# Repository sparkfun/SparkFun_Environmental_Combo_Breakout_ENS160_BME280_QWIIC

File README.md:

SparkFun Environmental Combo Breakout - ENS160/BME280 (Qwiic)
========================================

[*SparkFun Environmental Combo Breakout - ENS160/BME280 (Qwiic) (SEN-22858)*](https://www.sparkfun.com/products/22858)

Environmental sensor that includes the ENS160 and BME280.

Repository Contents
-------------------

* **/Documentation** - Data sheets, additional product information
* **/Hardware** - Eagle design files (.brd, .sch)
  * **/Production** - Production panel files (.brd)

Documentation
--------------
* **[ENS160 Library](https://github.com/sparkfun/SparkFun_Indoor_Air_Quality_Sensor-ENS160_Arduino_Library)** - Arduino library for the ENS160
* **[BME280 Library](https://github.com/sparkfun/SparkFun_BME280_Arduino_Library)** - Arduino library for the BME280
* **[Fritzing Part](https://github.com/sparkfun/Fritzing_Parts/blob/main/products/22858_sfe_qwiic_environmental_combo_ens160_bme280.fzpz)** - Fritzing Part for the Environmental Combo Breakout - ENS160/BME280.
* **[Hookup Guide](http://docs.sparkfun.com/SparkFun_Environmental_Combo_Breakout_ENS160_BME280_QWIIC/)** - Basic hookup guide for the Environmental Combo Breakout - ENS160/BME280.

Product Versions
----------------
* [SEN-22858](https://www.sparkfun.com/products/22858) - v1.1

Version History
---------------
* v1.0 - Initial Release

License Information
-------------------

This product is _**open source**_!

Please review the LICENSE.md file for license information.

If you have any questions or concerns on licensing, please contact technical support on our [SparkFun forums](https://forum.sparkfun.com/viewforum.php?f=152).

Distributed as-is; no warranty is given.

- Your friends at SparkFun.

_<COLLABORATION CREDIT>_

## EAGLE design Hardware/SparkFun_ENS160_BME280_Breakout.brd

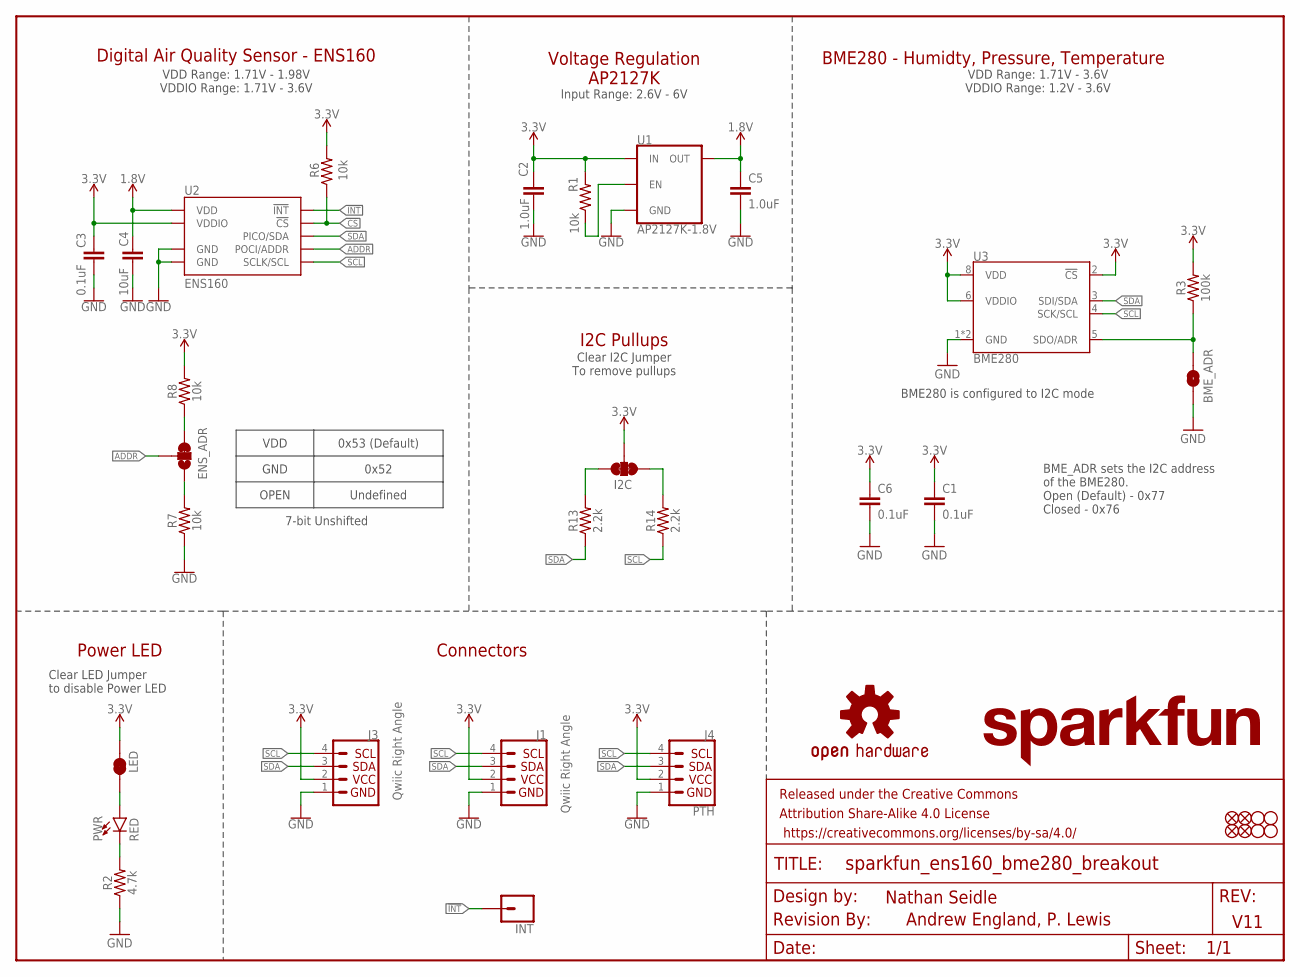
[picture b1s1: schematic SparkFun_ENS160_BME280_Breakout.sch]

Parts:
BME_ADR: JUMPER-SMT_2_NO_SILK; SMT-JUMPER_2_NO_SILK
C1, C3, C6: 0.1uF; 0402-TIGHT
C2, C5: 1.0uF; 0402-TIGHT
C4: 10uF; 0402-TIGHT
ENS_ADR: JUMPER-SMT_3_1-NC_TRACE_SILK; SMT-JUMPER_3_1-NC_TRACE_SILK
FD1, FD2, FD3, FD4: FIDUCIAL1X2; FIDUCIAL-1X2
FRAME1: FRAME-LETTER; CREATIVE_COMMONS
H1, H2, H3, H4: STAND-OFF
I2C: JUMPER-SMT_3_2-NC_TRACE_SILK; SMT-JUMPER_3_2-NC_TRACE_SILK
INT: CONN_01PTH_NO_SILK_STAND; 1X01_NO_SILK_STAND
J1, J3: Qwiic Right Angle; JST04_1MM_RA
J4: PTH; 1X04_NO_SILK
LED: JUMPER-SMT_2_NC_TRACE_SILK; SMT-JUMPER_2_NC_TRACE_SILK
LOGO1: SFE_LOGO_NAME.1_INCH; SFE_LOGO_NAME_.1
LOGO2: REVISION
LOGO4: OSHW-LOGOS; OSHW-LOGO-S
PWR: RED; LED-0603
R1, R6, R7, R8: 10k; 0402-TIGHT
R2: 4.7k; 0402-TIGHT
R3: 100k; 0402-TIGHT
R13, R14: 2.2k; 0402-TIGHT
U1: AP2127K-1.8V; SOT23-5
U2: ENS160; LGA-9
U3: BME280; LGA-8-2.5X2.5

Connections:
1.8V: C4.1, C5.1, U1.5 (OUT), U2.P4 (VDD)
3.3V: C1.1, C2.1, C3.1, C6.1, I2C.2, J1.2, J3.2, J4.2, LED.1, R1.2, R3.2, R6.2, R8.2, U1.1 (IN), U2.P5 (VDDIO), U3.2 (!CS), U3.6 (VDDIO), U3.8 (VDD)
!CS!: R6.1, U2.P7 (!CS!)
!INT!: INT.1, U2.P6 (!INT!)
ADDR: ENS_ADR.2, U2.P3 (POCI/ADDR)
GND: BME_ADR.1, C1.2, C2.2, C3.2, C4.2, C5.2, C6.2, J1.1, J3.1, J4.1, R2.1, R7.1, U1.2 (GND), U2.P8 (GND), U2.P9 (GND), U3.1 (GND), U3.7 (GND)
unnamed: ENS_ADR.3, R8.1
unnamed: R1.1, U1.3 (EN)
unnamed: I2C.3, R13.2
unnamed: I2C.1, R14.2
unnamed: PWR.C, R2.2
unnamed: ENS_ADR.1, R7.2
unnamed: LED.2, PWR.A
SCL: J1.4, J3.4, J4.4, R14.1, U2.P2 (SCLK/SCL), U3.4 (SCK/SCL)
SDA: J1.3, J3.3, J4.3, R13.1, U2.P1 (PICO/SDA), U3.3 (SDI/SDA)
SDO/ADR: BME_ADR.2, R3.1, U3.5 (SDO/ADR)

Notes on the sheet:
Clear I2C Jumper To remove pullups
V11
Nathan Seidle
BME_ADR sets the I2C address of the BME280. Open (Default) - 0x77 Closed - 0x76
BME280 is configured to I2C mode
BME280 - Humidty, Pressure, Temperature
Andrew England, P. Lewis
Digital Air Quality Sensor - ENS160
VDD Range: 1.71V - 1.98V VDDIO Range: 1.71V - 3.6V
VDD
GND
OPEN
0x52
0x53 (Default)
Undefined
7-bit Unshifted
Voltage Regulation AP2127K
Input Range: 2.6V - 6V
Clear LED Jumper to disable Power LED
Power LED
I2C Pullups
Connectors
VDD Range: 1.71V - 3.6V VDDIO Range: 1.2V - 3.6V

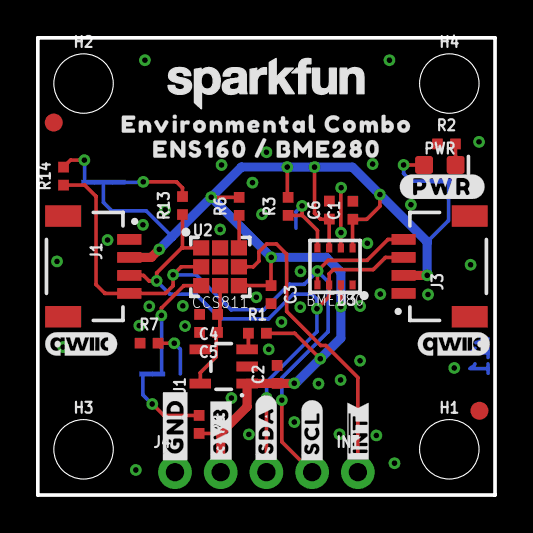
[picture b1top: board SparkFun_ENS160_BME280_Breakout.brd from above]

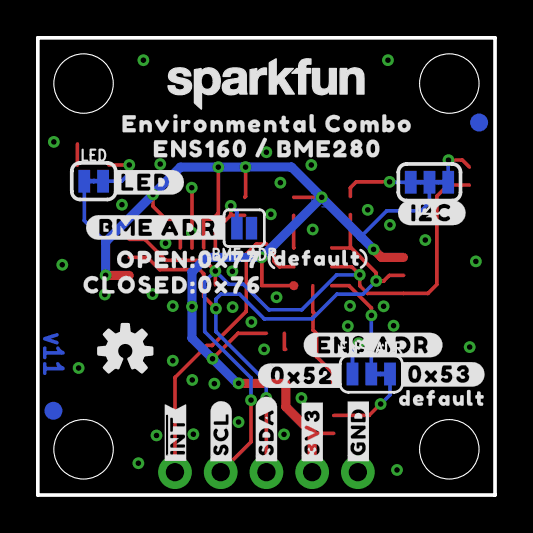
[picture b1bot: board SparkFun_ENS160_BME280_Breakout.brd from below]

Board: 2 copper layers, 25.4 x 25.4 mm, 67 parts (25 on the bottom side), 16 nets.

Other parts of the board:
LOGO3: SFE_LOGO_NAME.1_INCH; SFE_LOGO_NAME_.1@1
U$1: #BME_ADR#0
U$2: #0X53#0
U$3: #0X52#0
U$4: ##INT##6
U$5: #ENS_ADR#0
U$6: #I2C#0
U$7, U$11: ENVIRONMENTAL_COMBO0
U$8: #SCL#4
U$9: #GND#2
U$10, U$12: ENS160_#_BME2800
U$13, U$61: DEFAULT0
U$14: #SDA#3
U$15: #PWR#0
U$16: OPEN#0X770
U$17: CLOSED#0X760
U$18: #LED#0
U$20, U$21: QWIIC_4MM
U$27, U$46: #3V3#874
U$45: #GND#864
U$47: #SDA#874
U$48: #SCL#875
U$51: ##INT##877
U$59: ORDERING_INSTRUCTIONS

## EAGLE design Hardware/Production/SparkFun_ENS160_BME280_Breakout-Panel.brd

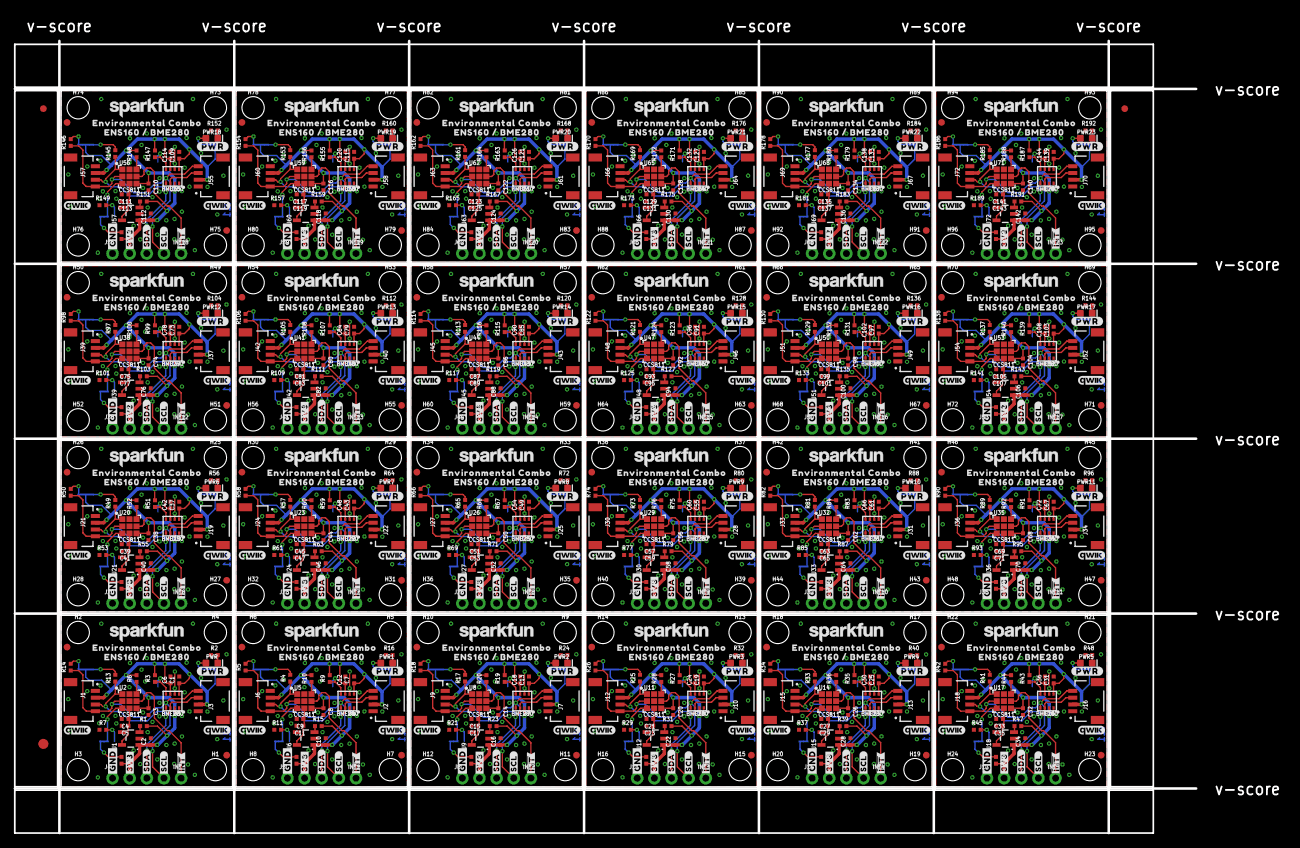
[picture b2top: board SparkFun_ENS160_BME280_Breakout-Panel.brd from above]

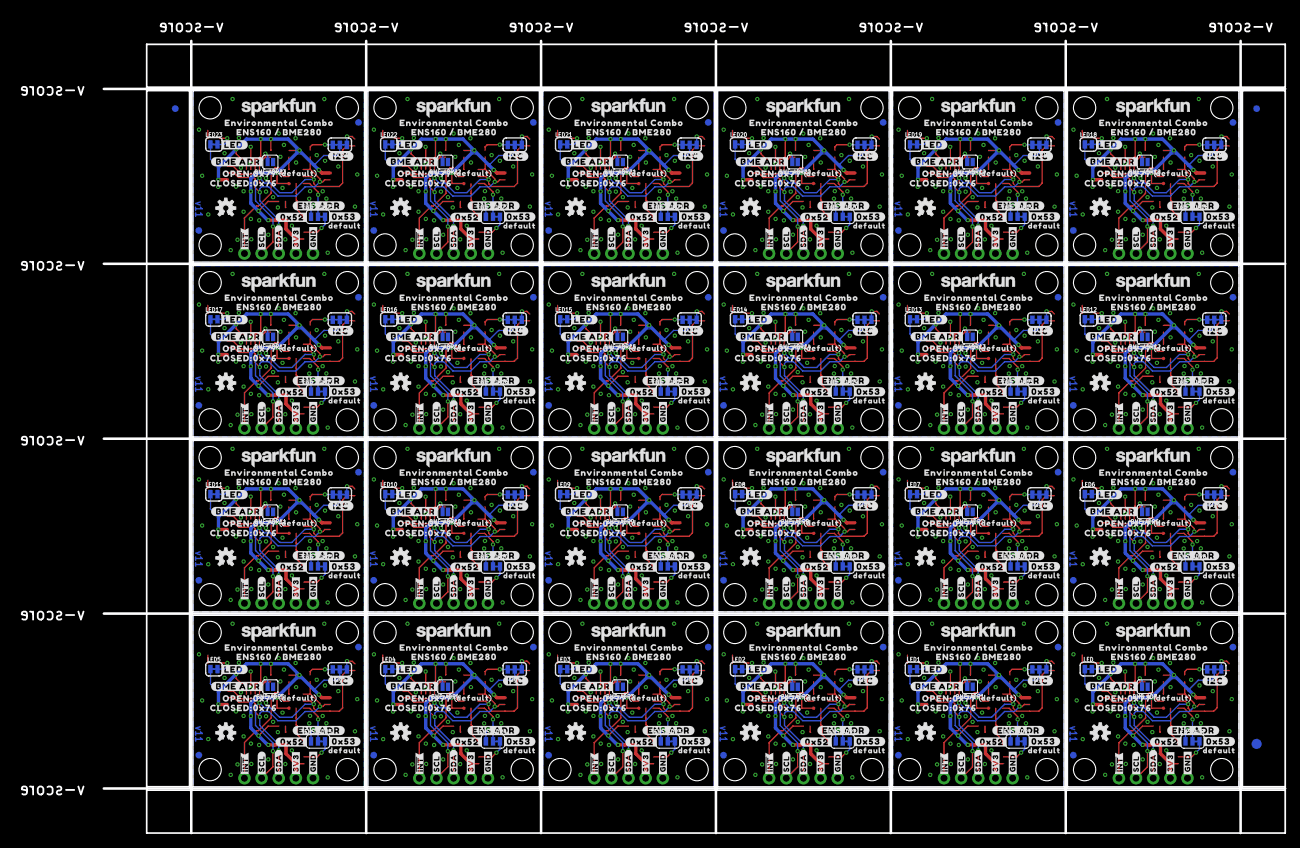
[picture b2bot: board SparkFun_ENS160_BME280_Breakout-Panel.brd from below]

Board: 2 copper layers, 188.2 x 121.2 mm, 1566 parts (603 on the bottom side), 384 nets.

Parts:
BME_ADR, BME_ADR1, BME_ADR2, BME_ADR3, BME_ADR4, BME_ADR5, BME_ADR6, BME_ADR7, BME_ADR8, BME_ADR9, BME_ADR10, BME_ADR11, BME_ADR12, BME_ADR13, BME_ADR14, BME_ADR15, BME_ADR16, BME_ADR17, BME_ADR18, BME_ADR19, BME_ADR20, BME_ADR21, BME_ADR22, BME_ADR23: SMT-JUMPER_2_NO_SILK
C1, C3, C6, C7, C8, C12, C13, C14, C18, C19, C20, C24, C25, C26, C30, C31, C32, C36, C37, C38, C42, C43, C44, C48, C49, C50, C54, C55, C56, C60, C61, C62, C66, C67, C68, C72, C73, C74, C78, C79, C80, C84, C85, C86, C90, C91, C92, C96, C97, C98, C102, C103, C104, C108, C109, C110, C114, C115, C116, C120, C121, C122, C126, C127, C128, C132, C133, C134, C138, C139, C140, C144: 0.1uF; 0402-TIGHT
C2, C5, C10, C11, C16, C17, C22, C23, C28, C29, C34, C35, C40, C41, C46, C47, C52, C53, C58, C59, C64, C65, C70, C71, C76, C77, C82, C83, C88, C89, C94, C95, C100, C101, C106, C107, C112, C113, C118, C119, C124, C125, C130, C131, C136, C137, C142, C143: 1.0uF; 0402-TIGHT
C4, C9, C15, C21, C27, C33, C39, C45, C51, C57, C63, C69, C75, C81, C87, C93, C99, C105, C111, C117, C123, C129, C135, C141: 10uF; 0402-TIGHT
E$1, E$2, E$3, E$4: FIDUCIAL-1X2
E$5, E$6: FIDUCIAL-1.5X3
ENS_ADR, ENS_ADR1, ENS_ADR2, ENS_ADR3, ENS_ADR4, ENS_ADR5, ENS_ADR6, ENS_ADR7, ENS_ADR8, ENS_ADR9, ENS_ADR10, ENS_ADR11, ENS_ADR12, ENS_ADR13, ENS_ADR14, ENS_ADR15, ENS_ADR16, ENS_ADR17, ENS_ADR18, ENS_ADR19, ENS_ADR20, ENS_ADR21, ENS_ADR22, ENS_ADR23: JUMPER-SMT_3_1-NC_TRACE_SILK; SMT-JUMPER_3_1-NC_TRACE_SILK
FD1, FD2, FD3, FD4, FD5, FD6, FD7, FD8, FD9, FD10, FD11, FD12, FD13, FD14, FD15, FD16, FD17, FD18, FD19, FD20, FD21, FD22, FD23, FD24, FD25, FD26, FD27, FD28, FD29, FD30, FD31, FD32, FD33, FD34, FD35, FD36, FD37, FD38, FD39, FD40, FD41, FD42, FD43, FD44, FD45, FD46, FD47, FD48, FD49, FD50, FD51, FD52, FD53, FD54, FD55, FD56, FD57, FD58, FD59, FD60, FD61, FD62, FD63, FD64, FD65, FD66, FD67, FD68, FD69, FD70, FD71, FD72, FD73, FD74, FD75, FD76, FD77, FD78, FD79, FD80, FD81, FD82, FD83, FD84, FD85, FD86, FD87, FD88, FD89, FD90, FD91, FD92, FD93, FD94, FD95, FD96: FIDUCIAL1X2; FIDUCIAL-1X2
H1, H2, H3, H4, H5, H6, H7, H8, H9, H10, H11, H12, H13, H14, H15, H16, H17, H18, H19, H20, H21, H22, H23, H24, H25, H26, H27, H28, H29, H30, H31, H32, H33, H34, H35, H36, H37, H38, H39, H40, H41, H42, H43, H44, H45, H46, H47, H48, H49, H50, H51, H52, H53, H54, H55, H56, H57, H58, H59, H60, H61, H62, H63, H64, H65, H66, H67, H68, H69, H70, H71, H72, H73, H74, H75, H76, H77, H78, H79, H80, H81, H82, H83, H84, H85, H86, H87, H88, H89, H90, H91, H92, H93, H94, H95, H96: STAND-OFF
I2C, I2C1, I2C2, I2C3, I2C4, I2C5, I2C6, I2C7, I2C8, I2C9, I2C10, I2C11, I2C12, I2C13, I2C14, I2C15, I2C16, I2C17, I2C18, I2C19, I2C20, I2C21, I2C22, I2C23: SMT-JUMPER_3_2-NC_TRACE_SILK
INT, INT1, INT2, INT3, INT4, INT5, INT6, INT7, INT8, INT9, INT10, INT11, INT12, INT13, INT14, INT15, INT16, INT17, INT18, INT19, INT20, INT21, INT22, INT23: 1X01_NO_SILK_STAND
J1, J2, J3, J6, J7, J9, J10, J12, J13, J15, J16, J18, J19, J21, J22, J24, J25, J27, J28, J30, J31, J33, J34, J36, J37, J39, J40, J42, J43, J45, J46, J48, J49, J51, J52, J54, J55, J57, J58, J60, J61, J63, J64, J66, J67, J69, J70, J72: Qwiic Right Angle; JST04_1MM_RA
J4, J5, J8, J11, J14, J17, J20, J23, J26, J29, J32, J35, J38, J41, J44, J47, J50, J53, J56, J59, J62, J65, J68, J71: PTH; 1X04_NO_SILK
LED, LED1, LED2, LED3, LED4, LED5, LED6, LED7, LED8, LED9, LED10, LED11, LED12, LED13, LED14, LED15, LED16, LED17, LED18, LED19, LED20, LED21, LED22, LED23: SMT-JUMPER_2_NC_TRACE_SILK
LOGO1, LOGO7, LOGO11, LOGO15, LOGO19, LOGO23, LOGO27, LOGO31, LOGO35, LOGO39, LOGO43, LOGO47, LOGO51, LOGO55, LOGO59, LOGO63, LOGO67, LOGO71, LOGO75, LOGO79, LOGO83, LOGO87, LOGO91, LOGO95: SFE_LOGO_NAME.1_INCH; SFE_LOGO_NAME_.1
LOGO2, LOGO6, LOGO10, LOGO14, LOGO18, LOGO22, LOGO26, LOGO30, LOGO34, LOGO38, LOGO42, LOGO46, LOGO50, LOGO54, LOGO58, LOGO62, LOGO66, LOGO70, LOGO74, LOGO78, LOGO82, LOGO86, LOGO90, LOGO94: REVISION
LOGO3, LOGO8, LOGO12, LOGO16, LOGO20, LOGO24, LOGO28, LOGO32, LOGO36, LOGO40, LOGO44, LOGO48, LOGO52, LOGO56, LOGO60, LOGO64, LOGO68, LOGO72, LOGO76, LOGO80, LOGO84, LOGO88, LOGO92, LOGO96: SFE_LOGO_NAME.1_INCH; SFE_LOGO_NAME_.1@1
LOGO4, LOGO5, LOGO9, LOGO13, LOGO17, LOGO21, LOGO25, LOGO29, LOGO33, LOGO37, LOGO41, LOGO45, LOGO49, LOGO53, LOGO57, LOGO61, LOGO65, LOGO69, LOGO73, LOGO77, LOGO81, LOGO85, LOGO89, LOGO93: OSHW-LOGOS; OSHW-LOGO-S
PWR, PWR1, PWR2, PWR3, PWR4, PWR5, PWR6, PWR7, PWR8, PWR9, PWR10, PWR11, PWR12, PWR13, PWR14, PWR15, PWR16, PWR17, PWR18, PWR19, PWR20, PWR21, PWR22, PWR23: RED; LED-0603
R1, R6, R7, R8, R10, R11, R12, R15, R20, R21, R22, R23, R28, R29, R30, R31, R36, R37, R38, R39, R44, R45, R46, R47, R52, R53, R54, R55, R60, R61, R62, R63, R68, R69, R70, R71, R76, R77, R78, R79, R84, R85, R86, R87, R92, R93, R94, R95, R100, R101, R102, R103, R108, R109, R110, R111, R116, R117, R118, R119, R124, R125, R126, R127, R132, R133, R134, R135, R140, R141, R142, R143, R148, R149, R150, R151, R156, R157, R158, R159, R164, R165, R166, R167, R172, R173, R174, R175, R180, R181, R182, R183, R188, R189, R190, R191: 10k; 0402-TIGHT
R2, R16, R24, R32, R40, R48, R56, R64, R72, R80, R88, R96, R104, R112, R120, R128, R136, R144, R152, R160, R168, R176, R184, R192: 4.7k; 0402-TIGHT
R3, R9, R19, R27, R35, R43, R51, R59, R67, R75, R83, R91, R99, R107, R115, R123, R131, R139, R147, R155, R163, R171, R179, R187: 100k; 0402-TIGHT
R4, R5, R13, R14, R17, R18, R25, R26, R33, R34, R41, R42, R49, R50, R57, R58, R65, R66, R73, R74, R81, R82, R89, R90, R97, R98, R105, R106, R113, R114, R121, R122, R129, R130, R137, R138, R145, R146, R153, R154, R161, R162, R169, R170, R177, R178, R185, R186: 2.2k; 0402-TIGHT
U1, U6, U9, U12, U15, U18, U21, U24, U27, U30, U33, U36, U39, U42, U45, U48, U51, U54, U57, U60, U63, U66, U69, U72: AP2127K-1.8V; SOT23-5
U2, U5, U8, U11, U14, U17, U20, U23, U26, U29, U32, U35, U38, U41, U44, U47, U50, U53, U56, U59, U62, U65, U68, U71: ENS160; LGA-9
U3, U4, U7, U10, U13, U16, U19, U22, U25, U28, U31, U34, U37, U40, U43, U46, U49, U52, U55, U58, U61, U64, U67, U70: BME280; LGA-8-2.5X2.5
U$1, U$41, U$74, U$101, U$128, U$155, U$182, U$209, U$236, U$263, U$290, U$317, U$344, U$371, U$398, U$425, U$452, U$479, U$506, U$533, U$560, U$587, U$614, U$641: #BME_ADR#0
U$2, U$32, U$65, U$92, U$119, U$146, U$173, U$200, U$227, U$254, U$281, U$308, U$335, U$362, U$389, U$416, U$443, U$470, U$497, U$524, U$551, U$578, U$605, U$632: #0X53#0
U$3, U$33, U$66, U$93, U$120, U$147, U$174, U$201, U$228, U$255, U$282, U$309, U$336, U$363, U$390, U$417, U$444, U$471, U$498, U$525, U$552, U$579, U$606, U$633: #0X52#0
U$4, U$31, U$64, U$91, U$118, U$145, U$172, U$199, U$226, U$253, U$280, U$307, U$334, U$361, U$388, U$415, U$442, U$469, U$496, U$523, U$550, U$577, U$604, U$631: ##INT##6
U$5, U$42, U$75, U$102, U$129, U$156, U$183, U$210, U$237, U$264, U$291, U$318, U$345, U$372, U$399, U$426, U$453, U$480, U$507, U$534, U$561, U$588, U$615, U$642: #ENS_ADR#0
U$6, U$34, U$67, U$94, U$121, U$148, U$175, U$202, U$229, U$256, U$283, U$310, U$337, U$364, U$391, U$418, U$445, U$472, U$499, U$526, U$553, U$580, U$607, U$634: #I2C#0
U$7, U$11, U$35, U$37, U$68, U$70, U$95, U$97, U$122, U$124, U$149, U$151, U$176, U$178, U$203, U$205, U$230, U$232, U$257, U$259, U$284, U$286, U$311, U$313, U$338, U$340, U$365, U$367, U$392, U$394, U$419, U$421, U$446, U$448, U$473, U$475, U$500, U$502, U$527, U$529, U$554, U$556, U$581, U$583, U$608, U$610, U$635, U$637: ENVIRONMENTAL_COMBO0
U$8, U$30, U$63, U$90, U$117, U$144, U$171, U$198, U$225, U$252, U$279, U$306, U$333, U$360, U$387, U$414, U$441, U$468, U$495, U$522, U$549, U$576, U$603, U$630: #SCL#4
U$9, U$28, U$60, U$88, U$115, U$142, U$169, U$196, U$223, U$250, U$277, U$304, U$331, U$358, U$385, U$412, U$439, U$466, U$493, U$520, U$547, U$574, U$601, U$628: #GND#2
U$10, U$12, U$36, U$38, U$69, U$71, U$96, U$98, U$123, U$125, U$150, U$152, U$177, U$179, U$204, U$206, U$231, U$233, U$258, U$260, U$285, U$287, U$312, U$314, U$339, U$341, U$366, U$368, U$393, U$395, U$420, U$422, U$447, U$449, U$474, U$476, U$501, U$503, U$528, U$530, U$555, U$557, U$582, U$584, U$609, U$611, U$636, U$638: ENS160_#_BME2800
U$13, U$43, U$44, U$61, U$76, U$77, U$103, U$104, U$130, U$131, U$157, U$158, U$184, U$185, U$211, U$212, U$238, U$239, U$265, U$266, U$292, U$293, U$319, U$320, U$346, U$347, U$373, U$374, U$400, U$401, U$427, U$428, U$454, U$455, U$481, U$482, U$508, U$509, U$535, U$536, U$562, U$563, U$589, U$590, U$616, U$617, U$643, U$644: DEFAULT0
U$14, U$29, U$62, U$89, U$116, U$143, U$170, U$197, U$224, U$251, U$278, U$305, U$332, U$359, U$386, U$413, U$440, U$467, U$494, U$521, U$548, U$575, U$602, U$629: #SDA#3
U$15, U$49, U$78, U$105, U$132, U$159, U$186, U$213, U$240, U$267, U$294, U$321, U$348, U$375, U$402, U$429, U$456, U$483, U$510, U$537, U$564, U$591, U$618, U$645: #PWR#0
U$16, U$39, U$72, U$99, U$126, U$153, U$180, U$207, U$234, U$261, U$288, U$315, U$342, U$369, U$396, U$423, U$450, U$477, U$504, U$531, U$558, U$585, U$612, U$639: OPEN#0X770
U$17, U$40, U$73, U$100, U$127, U$154, U$181, U$208, U$235, U$262, U$289, U$316, U$343, U$370, U$397, U$424, U$451, U$478, U$505, U$532, U$559, U$586, U$613, U$640: CLOSED#0X760
U$18, U$50, U$79, U$106, U$133, U$160, U$187, U$214, U$241, U$268, U$295, U$322, U$349, U$376, U$403, U$430, U$457, U$484, U$511, U$538, U$565, U$592, U$619, U$646: #LED#0
U$19, U$45, U$54, U$82, U$109, U$136, U$163, U$190, U$217, U$244, U$271, U$298, U$325, U$352, U$379, U$406, U$433, U$460, U$487, U$514, U$541, U$568, U$595, U$622: #GND#864
U$20, U$21, U$52, U$53, U$80, U$81, U$107, U$108, U$134, U$135, U$161, U$162, U$188, U$189, U$215, U$216, U$242, U$243, U$269, U$270, U$296, U$297, U$323, U$324, U$350, U$351, U$377, U$378, U$404, U$405, U$431, U$432, U$458, U$459, U$485, U$486, U$512, U$513, U$539, U$540, U$566, U$567, U$593, U$594, U$620, U$621, U$647, U$648: QWIIC_4MM
U$22, U$26, U$27, U$46, U$55, U$59, U$83, U$87, U$110, U$114, U$137, U$141, U$164, U$168, U$191, U$195, U$218, U$222, U$245, U$249, U$272, U$276, U$299, U$303, U$326, U$330, U$353, U$357, U$380, U$384, U$407, U$411, U$434, U$438, U$461, U$465, U$488, U$492, U$515, U$519, U$542, U$546, U$569, U$573, U$596, U$600, U$623, U$627: #3V3#874
U$23, U$47, U$56, U$84, U$111, U$138, U$165, U$192, U$219, U$246, U$273, U$300, U$327, U$354, U$381, U$408, U$435, U$462, U$489, U$516, U$543, U$570, U$597, U$624: #SDA#874
U$24, U$48, U$57, U$85, U$112, U$139, U$166, U$193, U$220, U$247, U$274, U$301, U$328, U$355, U$382, U$409, U$436, U$463, U$490, U$517, U$544, U$571, U$598, U$625: #SCL#875
U$25, U$51, U$58, U$86, U$113, U$140, U$167, U$194, U$221, U$248, U$275, U$302, U$329, U$356, U$383, U$410, U$437, U$464, U$491, U$518, U$545, U$572, U$599, U$626: ##INT##877

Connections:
1.8V: C4.1, C5.1, U1.5, U2.P4
1.8V1: C9.1, C11.1, U5.P4, U6.5
1.8V2: C15.1, C17.1, U8.P4, U9.5
1.8V3: C21.1, C23.1, U11.P4, U12.5
1.8V4: C27.1, C29.1, U14.P4, U15.5
1.8V5: C33.1, C35.1, U17.P4, U18.5
1.8V6: C39.1, C41.1, U20.P4, U21.5
1.8V7: C45.1, C47.1, U23.P4, U24.5
1.8V8: C51.1, C53.1, U26.P4, U27.5
1.8V9: C57.1, C59.1, U29.P4, U30.5
1.8V10: C63.1, C65.1, U32.P4, U33.5
1.8V11: C69.1, C71.1, U35.P4, U36.5
1.8V12: C75.1, C77.1, U38.P4, U39.5
1.8V13: C81.1, C83.1, U41.P4, U42.5
1.8V14: C87.1, C89.1, U44.P4, U45.5
1.8V15: C93.1, C95.1, U47.P4, U48.5
1.8V16: C99.1, C101.1, U50.P4, U51.5
1.8V17: C105.1, C107.1, U53.P4, U54.5
1.8V18: C111.1, C113.1, U56.P4, U57.5
1.8V19: C117.1, C119.1, U59.P4, U60.5
1.8V20: C123.1, C125.1, U62.P4, U63.5
1.8V21: C129.1, C131.1, U65.P4, U66.5
1.8V22: C135.1, C137.1, U68.P4, U69.5
1.8V23: C141.1, C143.1, U71.P4, U72.5
3.3V: C1.1, C2.1, C3.1, C6.1, I2C.2, J1.2, J3.2, J4.2, LED.1, R1.2, R3.2, R6.2, R8.2, U1.1, U2.P5, U3.2, U3.6, U3.8
3.3V1: C7.1, C8.1, C10.1, C12.1, I2C1.2, J2.2, J5.2, J6.2, LED1.1, R9.2, R10.2, R12.2, R15.2, U4.2, U4.6, U4.8, U5.P5, U6.1
3.3V2: C13.1, C14.1, C16.1, C18.1, I2C2.2, J7.2, J8.2, J9.2, LED2.1, R19.2, R20.2, R22.2, R23.2, U7.2, U7.6, U7.8, U8.P5, U9.1
3.3V3: C19.1, C20.1, C22.1, C24.1, I2C3.2, J10.2, J11.2, J12.2, LED3.1, R27.2, R28.2, R30.2, R31.2, U10.2, U10.6, U10.8, U11.P5, U12.1
3.3V4: C25.1, C26.1, C28.1, C30.1, I2C4.2, J13.2, J14.2, J15.2, LED4.1, R35.2, R36.2, R38.2, R39.2, U13.2, U13.6, U13.8, U14.P5, U15.1
3.3V5: C31.1, C32.1, C34.1, C36.1, I2C5.2, J16.2, J17.2, J18.2, LED5.1, R43.2, R44.2, R46.2, R47.2, U16.2, U16.6, U16.8, U17.P5, U18.1
3.3V6: C37.1, C38.1, C40.1, C42.1, I2C6.2, J19.2, J20.2, J21.2, LED6.1, R51.2, R52.2, R54.2, R55.2, U19.2, U19.6, U19.8, U20.P5, U21.1
3.3V7: C43.1, C44.1, C46.1, C48.1, I2C7.2, J22.2, J23.2, J24.2, LED7.1, R59.2, R60.2, R62.2, R63.2, U22.2, U22.6, U22.8, U23.P5, U24.1
3.3V8: C49.1, C50.1, C52.1, C54.1, I2C8.2, J25.2, J26.2, J27.2, LED8.1, R67.2, R68.2, R70.2, R71.2, U25.2, U25.6, U25.8, U26.P5, U27.1
3.3V9: C55.1, C56.1, C58.1, C60.1, I2C9.2, J28.2, J29.2, J30.2, LED9.1, R75.2, R76.2, R78.2, R79.2, U28.2, U28.6, U28.8, U29.P5, U30.1
3.3V10: C61.1, C62.1, C64.1, C66.1, I2C10.2, J31.2, J32.2, J33.2, LED10.1, R83.2, R84.2, R86.2, R87.2, U31.2, U31.6, U31.8, U32.P5, U33.1
3.3V11: C67.1, C68.1, C70.1, C72.1, I2C11.2, J34.2, J35.2, J36.2, LED11.1, R91.2, R92.2, R94.2, R95.2, U34.2, U34.6, U34.8, U35.P5, U36.1
3.3V12: C73.1, C74.1, C76.1, C78.1, I2C12.2, J37.2, J38.2, J39.2, LED12.1, R99.2, R100.2, R102.2, R103.2, U37.2, U37.6, U37.8, U38.P5, U39.1
3.3V13: C79.1, C80.1, C82.1, C84.1, I2C13.2, J40.2, J41.2, J42.2, LED13.1, R107.2, R108.2, R110.2, R111.2, U40.2, U40.6, U40.8, U41.P5, U42.1
3.3V14: C85.1, C86.1, C88.1, C90.1, I2C14.2, J43.2, J44.2, J45.2, LED14.1, R115.2, R116.2, R118.2, R119.2, U43.2, U43.6, U43.8, U44.P5, U45.1
3.3V15: C91.1, C92.1, C94.1, C96.1, I2C15.2, J46.2, J47.2, J48.2, LED15.1, R123.2, R124.2, R126.2, R127.2, U46.2, U46.6, U46.8, U47.P5, U48.1
3.3V16: C97.1, C98.1, C100.1, C102.1, I2C16.2, J49.2, J50.2, J51.2, LED16.1, R131.2, R132.2, R134.2, R135.2, U49.2, U49.6, U49.8, U50.P5, U51.1
3.3V17: C103.1, C104.1, C106.1, C108.1, I2C17.2, J52.2, J53.2, J54.2, LED17.1, R139.2, R140.2, R142.2, R143.2, U52.2, U52.6, U52.8, U53.P5, U54.1
3.3V18: C109.1, C110.1, C112.1, C114.1, I2C18.2, J55.2, J56.2, J57.2, LED18.1, R147.2, R148.2, R150.2, R151.2, U55.2, U55.6, U55.8, U56.P5, U57.1
3.3V19: C115.1, C116.1, C118.1, C120.1, I2C19.2, J58.2, J59.2, J60.2, LED19.1, R155.2, R156.2, R158.2, R159.2, U58.2, U58.6, U58.8, U59.P5, U60.1
3.3V20: C121.1, C122.1, C124.1, C126.1, I2C20.2, J61.2, J62.2, J63.2, LED20.1, R163.2, R164.2, R166.2, R167.2, U61.2, U61.6, U61.8, U62.P5, U63.1
3.3V21: C127.1, C128.1, C130.1, C132.1, I2C21.2, J64.2, J65.2, J66.2, LED21.1, R171.2, R172.2, R174.2, R175.2, U64.2, U64.6, U64.8, U65.P5, U66.1
3.3V22: C133.1, C134.1, C136.1, C138.1, I2C22.2, J67.2, J68.2, J69.2, LED22.1, R179.2, R180.2, R182.2, R183.2, U67.2, U67.6, U67.8, U68.P5, U69.1
3.3V23: C139.1, C140.1, C142.1, C144.1, I2C23.2, J70.2, J71.2, J72.2, LED23.1, R187.2, R188.2, R190.2, R191.2, U70.2, U70.6, U70.8, U71.P5, U72.1
!CS!: R6.1, U2.P7
!CS!1: R10.1, U5.P7
!CS!2: R20.1, U8.P7
!CS!3: R28.1, U11.P7
!CS!4: R36.1, U14.P7
!CS!5: R44.1, U17.P7
!CS!6: R52.1, U20.P7
!CS!7: R60.1, U23.P7
!CS!8: R68.1, U26.P7
!CS!9: R76.1, U29.P7
!CS!10: R84.1, U32.P7
!CS!11: R92.1, U35.P7
!CS!12: R100.1, U38.P7
!CS!13: R108.1, U41.P7
!CS!14: R116.1, U44.P7
!CS!15: R124.1, U47.P7
!CS!16: R132.1, U50.P7
!CS!17: R140.1, U53.P7
!CS!18: R148.1, U56.P7
!CS!19: R156.1, U59.P7
!CS!20: R164.1, U62.P7
!CS!21: R172.1, U65.P7
!CS!22: R180.1, U68.P7
!CS!23: R188.1, U71.P7
!INT!: INT.1, U2.P6
!INT!1: INT1.1, U5.P6
!INT!2: INT2.1, U8.P6
!INT!3: INT3.1, U11.P6
!INT!4: INT4.1, U14.P6
!INT!5: INT5.1, U17.P6
!INT!6: INT6.1, U20.P6
!INT!7: INT7.1, U23.P6
!INT!8: INT8.1, U26.P6
!INT!9: INT9.1, U29.P6
!INT!10: INT10.1, U32.P6
!INT!11: INT11.1, U35.P6
!INT!12: INT12.1, U38.P6
!INT!13: INT13.1, U41.P6
!INT!14: INT14.1, U44.P6
!INT!15: INT15.1, U47.P6
!INT!16: INT16.1, U50.P6
!INT!17: INT17.1, U53.P6
!INT!18: INT18.1, U56.P6
!INT!19: INT19.1, U59.P6
!INT!20: INT20.1, U62.P6
!INT!21: INT21.1, U65.P6
!INT!22: INT22.1, U68.P6
!INT!23: INT23.1, U71.P6
ADDR: ENS_ADR.2, U2.P3
ADDR1: ENS_ADR1.2, U5.P3
ADDR2: ENS_ADR2.2, U8.P3
ADDR3: ENS_ADR3.2, U11.P3
ADDR4: ENS_ADR4.2, U14.P3
ADDR5: ENS_ADR5.2, U17.P3
ADDR6: ENS_ADR6.2, U20.P3
ADDR7: ENS_ADR7.2, U23.P3
ADDR8: ENS_ADR8.2, U26.P3
ADDR9: ENS_ADR9.2, U29.P3
ADDR10: ENS_ADR10.2, U32.P3
ADDR11: ENS_ADR11.2, U35.P3
ADDR12: ENS_ADR12.2, U38.P3
ADDR13: ENS_ADR13.2, U41.P3
ADDR14: ENS_ADR14.2, U44.P3
ADDR15: ENS_ADR15.2, U47.P3
ADDR16: ENS_ADR16.2, U50.P3
ADDR17: ENS_ADR17.2, U53.P3
ADDR18: ENS_ADR18.2, U56.P3
ADDR19: ENS_ADR19.2, U59.P3
ADDR20: ENS_ADR20.2, U62.P3
ADDR21: ENS_ADR21.2, U65.P3
ADDR22: ENS_ADR22.2, U68.P3
ADDR23: ENS_ADR23.2, U71.P3
GND: BME_ADR.1, C1.2, C2.2, C3.2, C4.2, C5.2, C6.2, J1.1, J3.1, J4.1, R2.1, R7.1, U1.2, U2.P8, U2.P9, U3.1, U3.7
GND1: BME_ADR1.1, C7.2, C8.2, C9.2, C10.2, C11.2, C12.2, J2.1, J5.1, J6.1, R11.1, R16.1, U4.1, U4.7, U5.P8, U5.P9, U6.2
GND2: BME_ADR2.1, C13.2, C14.2, C15.2, C16.2, C17.2, C18.2, J7.1, J8.1, J9.1, R21.1, R24.1, U7.1, U7.7, U8.P8, U8.P9, U9.2
GND3: BME_ADR3.1, C19.2, C20.2, C21.2, C22.2, C23.2, C24.2, J10.1, J11.1, J12.1, R29.1, R32.1, U10.1, U10.7, U11.P8, U11.P9, U12.2
GND4: BME_ADR4.1, C25.2, C26.2, C27.2, C28.2, C29.2, C30.2, J13.1, J14.1, J15.1, R37.1, R40.1, U13.1, U13.7, U14.P8, U14.P9, U15.2
GND5: BME_ADR5.1, C31.2, C32.2, C33.2, C34.2, C35.2, C36.2, J16.1, J17.1, J18.1, R45.1, R48.1, U16.1, U16.7, U17.P8, U17.P9, U18.2
GND6: BME_ADR6.1, C37.2, C38.2, C39.2, C40.2, C41.2, C42.2, J19.1, J20.1, J21.1, R53.1, R56.1, U19.1, U19.7, U20.P8, U20.P9, U21.2
GND7: BME_ADR7.1, C43.2, C44.2, C45.2, C46.2, C47.2, C48.2, J22.1, J23.1, J24.1, R61.1, R64.1, U22.1, U22.7, U23.P8, U23.P9, U24.2
GND8: BME_ADR8.1, C49.2, C50.2, C51.2, C52.2, C53.2, C54.2, J25.1, J26.1, J27.1, R69.1, R72.1, U25.1, U25.7, U26.P8, U26.P9, U27.2
GND9: BME_ADR9.1, C55.2, C56.2, C57.2, C58.2, C59.2, C60.2, J28.1, J29.1, J30.1, R77.1, R80.1, U28.1, U28.7, U29.P8, U29.P9, U30.2
GND10: BME_ADR10.1, C61.2, C62.2, C63.2, C64.2, C65.2, C66.2, J31.1, J32.1, J33.1, R85.1, R88.1, U31.1, U31.7, U32.P8, U32.P9, U33.2
GND11: BME_ADR11.1, C67.2, C68.2, C69.2, C70.2, C71.2, C72.2, J34.1, J35.1, J36.1, R93.1, R96.1, U34.1, U34.7, U35.P8, U35.P9, U36.2
GND12: BME_ADR12.1, C73.2, C74.2, C75.2, C76.2, C77.2, C78.2, J37.1, J38.1, J39.1, R101.1, R104.1, U37.1, U37.7, U38.P8, U38.P9, U39.2
GND13: BME_ADR13.1, C79.2, C80.2, C81.2, C82.2, C83.2, C84.2, J40.1, J41.1, J42.1, R109.1, R112.1, U40.1, U40.7, U41.P8, U41.P9, U42.2
GND14: BME_ADR14.1, C85.2, C86.2, C87.2, C88.2, C89.2, C90.2, J43.1, J44.1, J45.1, R117.1, R120.1, U43.1, U43.7, U44.P8, U44.P9, U45.2
GND15: BME_ADR15.1, C91.2, C92.2, C93.2, C94.2, C95.2, C96.2, J46.1, J47.1, J48.1, R125.1, R128.1, U46.1, U46.7, U47.P8, U47.P9, U48.2
GND16: BME_ADR16.1, C97.2, C98.2, C99.2, C100.2, C101.2, C102.2, J49.1, J50.1, J51.1, R133.1, R136.1, U49.1, U49.7, U50.P8, U50.P9, U51.2
GND17: BME_ADR17.1, C103.2, C104.2, C105.2, C106.2, C107.2, C108.2, J52.1, J53.1, J54.1, R141.1, R144.1, U52.1, U52.7, U53.P8, U53.P9, U54.2
GND18: BME_ADR18.1, C109.2, C110.2, C111.2, C112.2, C113.2, C114.2, J55.1, J56.1, J57.1, R149.1, R152.1, U55.1, U55.7, U56.P8, U56.P9, U57.2
GND19: BME_ADR19.1, C115.2, C116.2, C117.2, C118.2, C119.2, C120.2, J58.1, J59.1, J60.1, R157.1, R160.1, U58.1, U58.7, U59.P8, U59.P9, U60.2
GND20: BME_ADR20.1, C121.2, C122.2, C123.2, C124.2, C125.2, C126.2, J61.1, J62.1, J63.1, R165.1, R168.1, U61.1, U61.7, U62.P8, U62.P9, U63.2
GND21: BME_ADR21.1, C127.2, C128.2, C129.2, C130.2, C131.2, C132.2, J64.1, J65.1, J66.1, R173.1, R176.1, U64.1, U64.7, U65.P8, U65.P9, U66.2
GND22: BME_ADR22.1, C133.2, C134.2, C135.2, C136.2, C137.2, C138.2, J67.1, J68.1, J69.1, R181.1, R184.1, U67.1, U67.7, U68.P8, U68.P9, U69.2
GND23: BME_ADR23.1, C139.2, C140.2, C141.2, C142.2, C143.2, C144.2, J70.1, J71.1, J72.1, R189.1, R192.1, U70.1, U70.7, U71.P8, U71.P9, U72.2
unnamed: I2C1.3, R4.2
unnamed: ENS_ADR.3, R8.1
unnamed: R1.1, U1.3
unnamed: I2C.3, R13.2
unnamed: I2C.1, R14.2
unnamed: PWR.C, R2.2
unnamed: ENS_ADR.1, R7.2
unnamed: LED.2, PWR.A
unnamed: I2C1.1, R5.2
unnamed: ENS_ADR1.3, R12.1
unnamed: ENS_ADR1.1, R11.2
unnamed: R15.1, U6.3
unnamed: PWR1.C, R16.2
unnamed: LED1.2, PWR1.A
unnamed: I2C2.3, R17.2
unnamed: I2C2.1, R18.2
unnamed: ENS_ADR2.3, R22.1
unnamed: ENS_ADR2.1, R21.2
unnamed: R23.1, U9.3
unnamed: PWR2.C, R24.2
unnamed: LED2.2, PWR2.A
unnamed: I2C3.3, R25.2
unnamed: I2C3.1, R26.2
unnamed: ENS_ADR3.3, R30.1
unnamed: ENS_ADR3.1, R29.2
unnamed: R31.1, U12.3
unnamed: PWR3.C, R32.2
unnamed: LED3.2, PWR3.A
unnamed: I2C4.3, R33.2
unnamed: I2C4.1, R34.2
unnamed: ENS_ADR4.3, R38.1
unnamed: ENS_ADR4.1, R37.2
unnamed: R39.1, U15.3
unnamed: PWR4.C, R40.2
unnamed: LED4.2, PWR4.A
unnamed: I2C5.3, R41.2
unnamed: I2C5.1, R42.2
unnamed: ENS_ADR5.3, R46.1
unnamed: ENS_ADR5.1, R45.2
unnamed: R47.1, U18.3
unnamed: PWR5.C, R48.2
unnamed: LED5.2, PWR5.A
unnamed: I2C6.3, R49.2
unnamed: I2C6.1, R50.2
unnamed: ENS_ADR6.3, R54.1
unnamed: ENS_ADR6.1, R53.2
unnamed: R55.1, U21.3
unnamed: PWR6.C, R56.2
unnamed: LED6.2, PWR6.A
unnamed: I2C7.3, R57.2
unnamed: I2C7.1, R58.2
unnamed: ENS_ADR7.3, R62.1
unnamed: ENS_ADR7.1, R61.2
unnamed: R63.1, U24.3
unnamed: PWR7.C, R64.2
unnamed: LED7.2, PWR7.A
unnamed: I2C8.3, R65.2
unnamed: I2C8.1, R66.2
unnamed: ENS_ADR8.3, R70.1
unnamed: ENS_ADR8.1, R69.2
unnamed: R71.1, U27.3
unnamed: PWR8.C, R72.2
unnamed: LED8.2, PWR8.A
unnamed: I2C9.3, R73.2
unnamed: I2C9.1, R74.2
unnamed: ENS_ADR9.3, R78.1
unnamed: ENS_ADR9.1, R77.2
unnamed: R79.1, U30.3
unnamed: PWR9.C, R80.2
unnamed: LED9.2, PWR9.A
unnamed: I2C10.3, R81.2
unnamed: I2C10.1, R82.2
unnamed: ENS_ADR10.3, R86.1
unnamed: ENS_ADR10.1, R85.2
unnamed: R87.1, U33.3
unnamed: PWR10.C, R88.2
unnamed: LED10.2, PWR10.A
unnamed: I2C11.3, R89.2
unnamed: I2C11.1, R90.2
unnamed: ENS_ADR11.3, R94.1
unnamed: ENS_ADR11.1, R93.2
unnamed: R95.1, U36.3
unnamed: PWR11.C, R96.2
unnamed: LED11.2, PWR11.A
unnamed: I2C12.3, R97.2
unnamed: I2C12.1, R98.2
unnamed: ENS_ADR12.3, R102.1
unnamed: ENS_ADR12.1, R101.2
unnamed: R103.1, U39.3
unnamed: PWR12.C, R104.2
unnamed: LED12.2, PWR12.A
unnamed: I2C13.3, R105.2
unnamed: I2C13.1, R106.2
unnamed: ENS_ADR13.3, R110.1
unnamed: ENS_ADR13.1, R109.2
unnamed: R111.1, U42.3
unnamed: PWR13.C, R112.2
unnamed: LED13.2, PWR13.A
unnamed: I2C14.3, R113.2
unnamed: I2C14.1, R114.2
unnamed: ENS_ADR14.3, R118.1
unnamed: ENS_ADR14.1, R117.2
unnamed: R119.1, U45.3
unnamed: PWR14.C, R120.2
unnamed: LED14.2, PWR14.A
unnamed: I2C15.3, R121.2
unnamed: I2C15.1, R122.2
unnamed: ENS_ADR15.3, R126.1
unnamed: ENS_ADR15.1, R125.2
unnamed: R127.1, U48.3
unnamed: PWR15.C, R128.2
unnamed: LED15.2, PWR15.A
unnamed: I2C16.3, R129.2
unnamed: I2C16.1, R130.2
unnamed: ENS_ADR16.3, R134.1
unnamed: ENS_ADR16.1, R133.2
unnamed: R135.1, U51.3
unnamed: PWR16.C, R136.2
unnamed: LED16.2, PWR16.A
unnamed: I2C17.3, R137.2
unnamed: I2C17.1, R138.2
unnamed: ENS_ADR17.3, R142.1
unnamed: ENS_ADR17.1, R141.2
unnamed: R143.1, U54.3
unnamed: PWR17.C, R144.2
unnamed: LED17.2, PWR17.A
unnamed: I2C18.3, R145.2
unnamed: I2C18.1, R146.2
unnamed: ENS_ADR18.3, R150.1
unnamed: ENS_ADR18.1, R149.2
unnamed: R151.1, U57.3
unnamed: PWR18.C, R152.2
unnamed: LED18.2, PWR18.A
unnamed: I2C19.3, R153.2
unnamed: I2C19.1, R154.2
unnamed: ENS_ADR19.3, R158.1
unnamed: ENS_ADR19.1, R157.2
unnamed: R159.1, U60.3
unnamed: PWR19.C, R160.2
unnamed: LED19.2, PWR19.A
unnamed: I2C20.3, R161.2
unnamed: I2C20.1, R162.2
unnamed: ENS_ADR20.3, R166.1
unnamed: ENS_ADR20.1, R165.2
unnamed: R167.1, U63.3
unnamed: PWR20.C, R168.2
unnamed: LED20.2, PWR20.A
unnamed: I2C21.3, R169.2
unnamed: I2C21.1, R170.2
unnamed: ENS_ADR21.3, R174.1
unnamed: ENS_ADR21.1, R173.2
unnamed: R175.1, U66.3
unnamed: PWR21.C, R176.2
unnamed: LED21.2, PWR21.A
unnamed: I2C22.3, R177.2
unnamed: I2C22.1, R178.2
unnamed: ENS_ADR22.3, R182.1
unnamed: ENS_ADR22.1, R181.2
unnamed: R183.1, U69.3
unnamed: PWR22.C, R184.2
unnamed: LED22.2, PWR22.A
unnamed: I2C23.3, R185.2
unnamed: I2C23.1, R186.2
unnamed: ENS_ADR23.3, R190.1
unnamed: ENS_ADR23.1, R189.2
unnamed: R191.1, U72.3
unnamed: PWR23.C, R192.2
unnamed: LED23.2, PWR23.A
SCL: J1.4, J3.4, J4.4, R14.1, U2.P2, U3.4
SCL1: J2.4, J5.4, J6.4, R5.1, U4.4, U5.P2
SCL2: J7.4, J8.4, J9.4, R18.1, U7.4, U8.P2
SCL3: J10.4, J11.4, J12.4, R26.1, U10.4, U11.P2
SCL4: J13.4, J14.4, J15.4, R34.1, U13.4, U14.P2
SCL5: J16.4, J17.4, J18.4, R42.1, U16.4, U17.P2
SCL6: J19.4, J20.4, J21.4, R50.1, U19.4, U20.P2
SCL7: J22.4, J23.4, J24.4, R58.1, U22.4, U23.P2
SCL8: J25.4, J26.4, J27.4, R66.1, U25.4, U26.P2
SCL9: J28.4, J29.4, J30.4, R74.1, U28.4, U29.P2
SCL10: J31.4, J32.4, J33.4, R82.1, U31.4, U32.P2
SCL11: J34.4, J35.4, J36.4, R90.1, U34.4, U35.P2
SCL12: J37.4, J38.4, J39.4, R98.1, U37.4, U38.P2
SCL13: J40.4, J41.4, J42.4, R106.1, U40.4, U41.P2
SCL14: J43.4, J44.4, J45.4, R114.1, U43.4, U44.P2
SCL15: J46.4, J47.4, J48.4, R122.1, U46.4, U47.P2
SCL16: J49.4, J50.4, J51.4, R130.1, U49.4, U50.P2
SCL17: J52.4, J53.4, J54.4, R138.1, U52.4, U53.P2
SCL18: J55.4, J56.4, J57.4, R146.1, U55.4, U56.P2
SCL19: J58.4, J59.4, J60.4, R154.1, U58.4, U59.P2
SCL20: J61.4, J62.4, J63.4, R162.1, U61.4, U62.P2
SCL21: J64.4, J65.4, J66.4, R170.1, U64.4, U65.P2
SCL22: J67.4, J68.4, J69.4, R178.1, U67.4, U68.P2
SCL23: J70.4, J71.4, J72.4, R186.1, U70.4, U71.P2
SDA: J1.3, J3.3, J4.3, R13.1, U2.P1, U3.3
SDA1: J2.3, J5.3, J6.3, R4.1, U4.3, U5.P1
SDA2: J7.3, J8.3, J9.3, R17.1, U7.3, U8.P1
SDA3: J10.3, J11.3, J12.3, R25.1, U10.3, U11.P1
SDA4: J13.3, J14.3, J15.3, R33.1, U13.3, U14.P1
SDA5: J16.3, J17.3, J18.3, R41.1, U16.3, U17.P1
SDA6: J19.3, J20.3, J21.3, R49.1, U19.3, U20.P1
SDA7: J22.3, J23.3, J24.3, R57.1, U22.3, U23.P1
SDA8: J25.3, J26.3, J27.3, R65.1, U25.3, U26.P1
SDA9: J28.3, J29.3, J30.3, R73.1, U28.3, U29.P1
SDA10: J31.3, J32.3, J33.3, R81.1, U31.3, U32.P1
SDA11: J34.3, J35.3, J36.3, R89.1, U34.3, U35.P1
SDA12: J37.3, J38.3, J39.3, R97.1, U37.3, U38.P1
SDA13: J40.3, J41.3, J42.3, R105.1, U40.3, U41.P1
SDA14: J43.3, J44.3, J45.3, R113.1, U43.3, U44.P1
SDA15: J46.3, J47.3, J48.3, R121.1, U46.3, U47.P1
SDA16: J49.3, J50.3, J51.3, R129.1, U49.3, U50.P1
SDA17: J52.3, J53.3, J54.3, R137.1, U52.3, U53.P1
SDA18: J55.3, J56.3, J57.3, R145.1, U55.3, U56.P1
SDA19: J58.3, J59.3, J60.3, R153.1, U58.3, U59.P1
SDA20: J61.3, J62.3, J63.3, R161.1, U61.3, U62.P1
SDA21: J64.3, J65.3, J66.3, R169.1, U64.3, U65.P1
SDA22: J67.3, J68.3, J69.3, R177.1, U67.3, U68.P1
SDA23: J70.3, J71.3, J72.3, R185.1, U70.3, U71.P1
SDO/ADR: BME_ADR.2, R3.1, U3.5
SDO/ADR1: BME_ADR1.2, R9.1, U4.5
SDO/ADR2: BME_ADR2.2, R19.1, U7.5
SDO/ADR3: BME_ADR3.2, R27.1, U10.5
SDO/ADR4: BME_ADR4.2, R35.1, U13.5
SDO/ADR5: BME_ADR5.2, R43.1, U16.5
SDO/ADR6: BME_ADR6.2, R51.1, U19.5
SDO/ADR7: BME_ADR7.2, R59.1, U22.5
SDO/ADR8: BME_ADR8.2, R67.1, U25.5
SDO/ADR9: BME_ADR9.2, R75.1, U28.5
SDO/ADR10: BME_ADR10.2, R83.1, U31.5
SDO/ADR11: BME_ADR11.2, R91.1, U34.5
SDO/ADR12: BME_ADR12.2, R99.1, U37.5
SDO/ADR13: BME_ADR13.2, R107.1, U40.5
SDO/ADR14: BME_ADR14.2, R115.1, U43.5
SDO/ADR15: BME_ADR15.2, R123.1, U46.5
SDO/ADR16: BME_ADR16.2, R131.1, U49.5
SDO/ADR17: BME_ADR17.2, R139.1, U52.5
SDO/ADR18: BME_ADR18.2, R147.1, U55.5
SDO/ADR19: BME_ADR19.2, R155.1, U58.5
SDO/ADR20: BME_ADR20.2, R163.1, U61.5
SDO/ADR21: BME_ADR21.2, R171.1, U64.5
SDO/ADR22: BME_ADR22.2, R179.1, U67.5
SDO/ADR23: BME_ADR23.2, R187.1, U70.5

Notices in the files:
parts and their libraries:
SparkFun-Aesthetics: Licensing: Creative Commons ShareAlike 4.0 International - https://creativecommons.org/licenses/by-sa/4.0
SparkFun-Aesthetics: Released under the Creative Commons Attribution Share-Alike 4.0 License
SparkFun-Aesthetics: https://creativecommons.org/licenses/by-sa/4.0
